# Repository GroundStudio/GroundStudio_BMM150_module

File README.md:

GroundStudio BMM150 module
====================================

Get it from [ardushop.ro](https://ardushop.ro/ro/118-groundstudio)

Explore all the GroundStudio products at [GroundStudio.ro](https://groundstudio.ro/)

Description
-------------------
Module based on the BMM150 three-axis geomagnetic sensor equiped with i2c 3v3 connectors.

Contents
-------------------

* [/Documentation](https://github.com/GroundStudio/GroundStudio_BMM150_module/tree/main/Documentation) -- Contains documentation written during creation of this repository, with readme.md index of its own!
* [/Firmware](https://github.com/GroundStudio/GroundStudio_BMM150_module/tree/main/Firmware) -- Firmware (bootloaders, etc)
* [/Hardware](https://github.com/GroundStudio/GroundStudio_BMM150_module/tree/main/Hardware) -- Schematics, layout.
* [/Libraries](https://github.com/GroundStudio/GroundStudio_BMM150_module/tree/main/Libraries) -- Arduino/CircuitPython libraries. 
* [/Tools](https://github.com/GroundStudio/GroundStudio_BMM150_module) -- Tools needed for compiling, uploading bootloader, etc.

Versions
-------------------
*(Not all tags shown)*
* [V0.0.1] Initial version

License
-------------------
This is released under the [Attribution-ShareAlike 4.0 International (CC BY-SA 4.0)](https://creativecommons.org/licenses/by-sa/4.0/) license. 
**You are welcome to use this for commercial purposes.**

Please consider contributing back to this project or others to help the open-source hardware community continue to thrive and grow! 
   
Certifications:   
[Open Source Hardware Association](https://certification.oshwa.org/ro000003.html)

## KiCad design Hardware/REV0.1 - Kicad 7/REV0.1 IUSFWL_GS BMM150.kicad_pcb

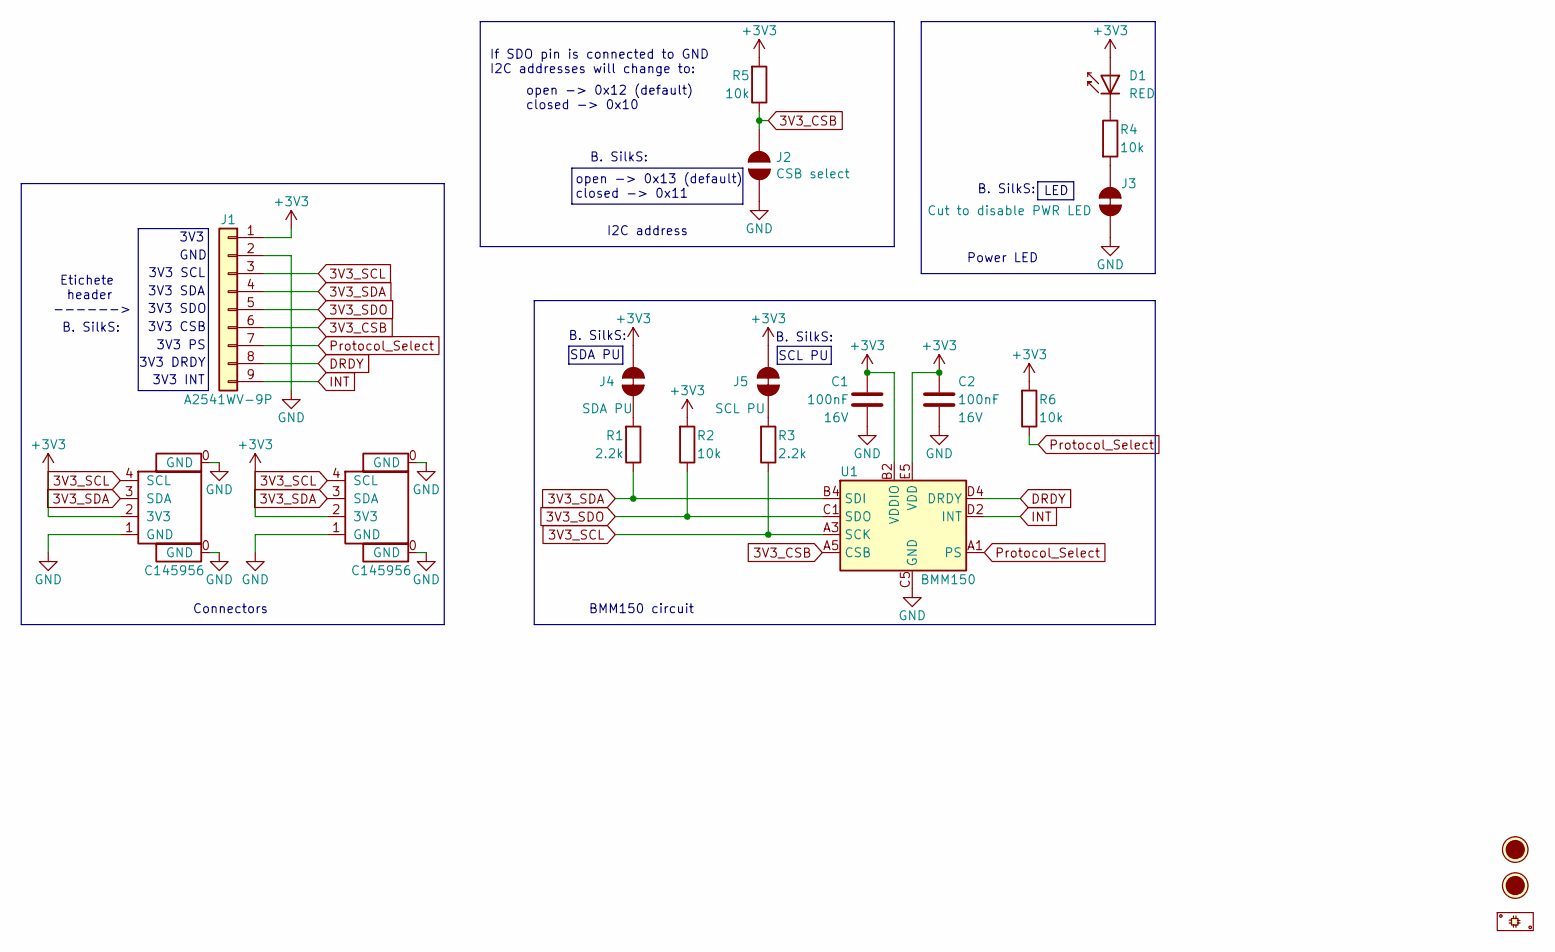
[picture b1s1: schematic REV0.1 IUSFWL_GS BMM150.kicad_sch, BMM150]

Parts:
C1, C2: C_0402_100nF_16V; C_0402; Rated voltage 16V; MPN 0402B104K160CT; LCSC C83056
D1: LED_0402_RED; LED_0402; MPN TZ-P2-0402RTIA1-0.45T; LCSC C779449
FID1, FID2: Fiducial; Fiducial_0.75mm_Mask1.5mm
J1: PinHeader_1x09_P2.54_V_M; PinHeader_1x09_P2.54mm_Vertical_Male; MPN A2541WV-9P; LCSC C225484
J2: CSB select; SolderJumper_NO
J3: Cut to disable PWR LED; SolderJumper_NC
J4: SDA PU; SolderJumper_NC
J5: SCL PU; SolderJumper_NC
P1: PCB; MPN IUSFWL_GS_PCB
R1, R3: R_0402_2.2k; R_0402; MPN RC-02W2201FT; LCSC C258093
R2, R4, R5, R6: R_0402_10k; R_0402; MPN 0402WGJ0103TCE; LCSC C25531
U1: WLCSP-12 BMM150; WLCSP-12_1.56x1.56mm_P0.4mm; MPN BMM150; LCSC C171681
X1, X2: SH_1x04_P1.0_H; SH__1x04_P1.00mm_Horizontal; MPN C145956; LCSC C145956

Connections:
3V3_CSB: J1.6, J2.1, R5.1, U1.A5 (CSB)
3V3_SCL: J1.3, R3.1, U1.A3 (SCK), X1.4 (SCL), X2.4 (SCL)
3V3_SDA: J1.4, R1.1, U1.B4 (SDI), X1.3 (SDA), X2.3 (SDA)
3V3_SDO: J1.5, R2.1, U1.C1 (SDO)
+3V3: C1.2, C2.2, D1.2 (A), J1.1, J4.2, J5.2, R2.2, R5.2, R6.2, U1.B2 (VDDIO), U1.E5 (VDD), X1.2 (3V3), X2.2 (3V3)
DRDY: J1.8, U1.D4 (DRDY)
GND: C1.1, C2.1, J1.2, J2.2, J3.2, U1.C5 (GND), U1.E1 (GND), U1.E3 (GND), X1.0 (GND), X1.1 (GND), X2.0 (GND), X2.1 (GND)
INT: J1.9, U1.D2 (INT)
unnamed: D1.1 (K), R4.1
unnamed: J3.1, R4.2
unnamed: J4.1, R1.2
unnamed: J5.1, R3.2
Protocol_Select: J1.7, R6.1, U1.A1 (PS)

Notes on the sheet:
3V3 SDO
3V3 CSB
3V3 INT
Etichete header ------>
SCL PU
3V3
3V3 PS
B. SilkS:
GND
3V3 SCL
Power LED
SDA PU
3V3 DRDY
3V3 SDA
open -> 0x13 (default) closed -> 0x11
open -> 0x12 (default) closed -> 0x10
If SDO pin is connected to GND I2C addresses will change to:
I2C address
LED
Connectors
BMM150 circuit

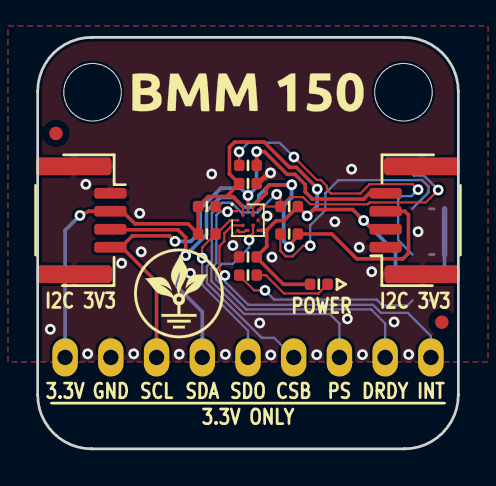
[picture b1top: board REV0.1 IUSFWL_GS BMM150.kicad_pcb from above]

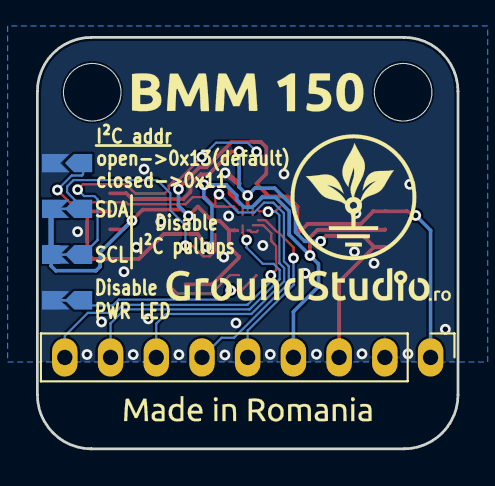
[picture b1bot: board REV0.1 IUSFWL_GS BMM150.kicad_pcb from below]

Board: 2 copper layers, 23.4 x 22.9 mm, 19 parts (5 on the bottom side), 13 nets.

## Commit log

2023-12-28 - initial commit
